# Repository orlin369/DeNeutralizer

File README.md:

# DeNeutralizer
DeNeutralizer is a magical home lighting control project. The project is dedicated to the installation of a Shelly relay module without the need for a neutral wire.

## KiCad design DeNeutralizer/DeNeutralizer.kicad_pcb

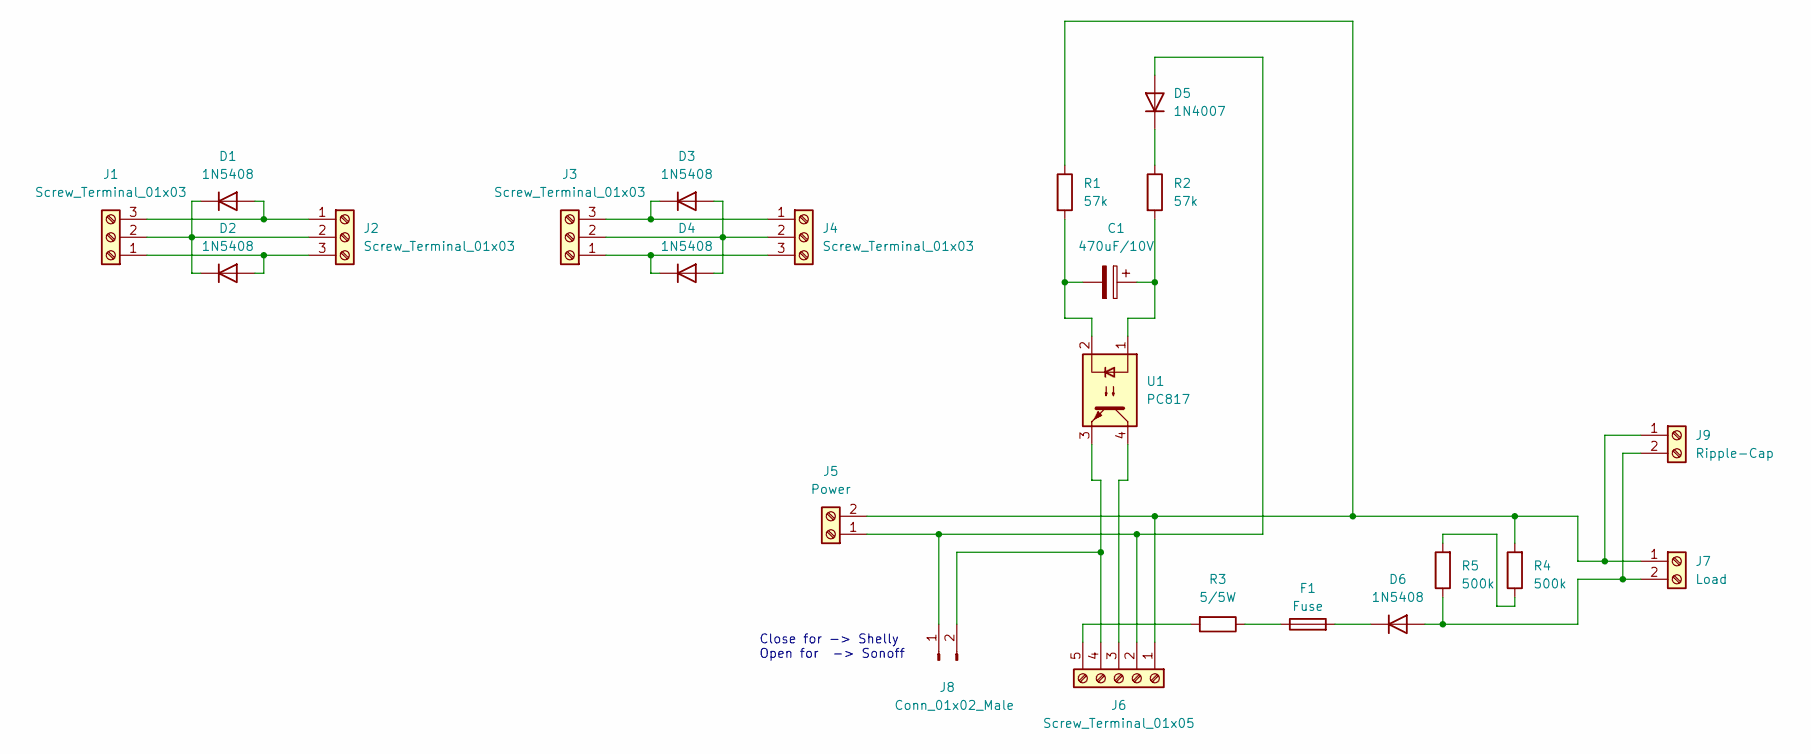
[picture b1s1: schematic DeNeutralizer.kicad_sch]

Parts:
C1: 470uF/10V; CP_Radial_D6.3mm_P2.50mm
D1, D2, D3, D4: 1N5408; D_DO-201AD_P5.08mm_Vertical_KathodeUp
D5: 1N4007; D_DO-41_SOD81_P2.54mm_Vertical_KathodeUp
D6: 1N5408; D_DO-201AD_P12.70mm_Horizontal
F1: Fuse
J1, J2, J3, J4: Screw_Terminal_01x03; TerminalBlock_bornier-3_P5.08mm
J5: Power; TerminalBlock_bornier-2_P5.08mm
J6: Screw_Terminal_01x05; TerminalBlock_bornier-5_P5.08mm
J7: Load; TerminalBlock_bornier-2_P5.08mm
J8: Conn_01x02_Male; PinHeader_1x02_P2.54mm_Vertical
J9: Ripple-Cap; TerminalBlock_bornier-2_P5.08mm
R1, R2: 57k; R_Axial_DIN0207_L6.3mm_D2.5mm_P2.54mm_Vertical
R3: 5/5W; R_Axial_Power_L25.0mm_W9.0mm_P27.94mm
R4, R5: 500k; R_Axial_DIN0207_L6.3mm_D2.5mm_P2.54mm_Vertical
U1: PC817; DIP-4_W7.62mm

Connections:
unnamed: C1.1, R2.2, U1.1
unnamed: C1.2, R1.2, U1.2
unnamed: D1.2 (A), J1.3, J2.1
unnamed: D1.1 (K), D2.1 (K), J1.2, J2.2
unnamed: D2.2 (A), J1.1, J2.3
unnamed: D3.2 (A), D4.2 (A), J3.2, J4.2
unnamed: D3.1 (K), J3.3, J4.1
unnamed: D4.1 (K), J3.1, J4.3
unnamed: D5.2 (A), J5.1, J6.2, J8.1
unnamed: D5.1 (K), R2.1
unnamed: D6.2 (A), J7.2, J9.2, R5.1
unnamed: D6.1 (K), F1.2
unnamed: F1.1, R3.1
unnamed: J5.2, J6.1, J7.1, J9.1, R1.1, R4.2
unnamed: J6.3, U1.4
unnamed: J6.4, J8.2, U1.3
unnamed: J6.5, R3.2
unnamed: R4.1, R5.2

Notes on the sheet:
Close for -> Shelly Open for -> Sonoff

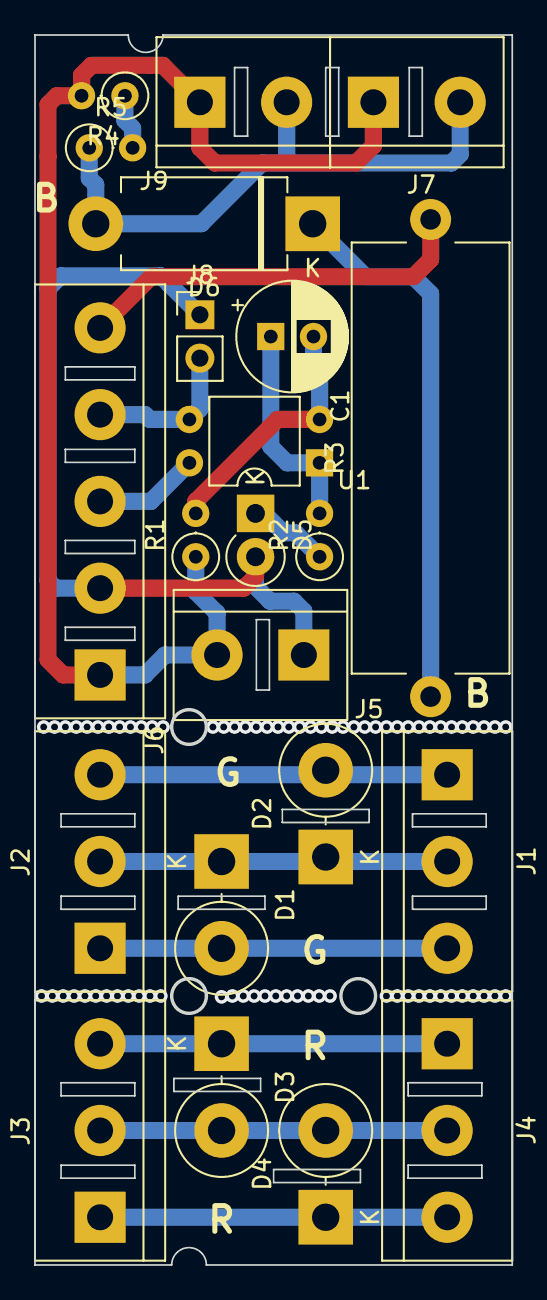
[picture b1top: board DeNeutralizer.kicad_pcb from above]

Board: 2 copper layers, 27.8 x 71.9 mm, 22 parts (0 on the bottom side), 16 nets.

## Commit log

2022-10-23 Add PCB design
2022-10-30 Update PCB contour
2022-10-30 Redesign the PCB
2022-10-30 Update components marks locations
2022-10-30 Add safety openings
2022-10-31 Update paths
2022-12-12 Add spark gaps
2023-01-19 Add BOM and backup
2023-02-06 Add jumper and for switcihing between modes and crt for external ripple capacitor
2023-02-19 Add 5W resistor insted 0.6W for serial protection
2023-02-19 Add Shelly 1 to the 3D model export
2023-03-31 Add backups
2023-03-31 Convert PCB to a new file format
2023-03-31 Make tha board as low profile as it can for this time :D
2023-03-31 Add two exports of the new low profile
2023-04-26 Add 3D model of the Shelly
